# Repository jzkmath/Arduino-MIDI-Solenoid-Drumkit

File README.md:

# Arduino-MIDI-Solenoid-Drumkit
Uses an Arduino Mega and a custom Shield PCB to drive 14 solenoids (RevA) or 32 solenoids (RevB) via MIDI

## Rev A:

## Rev B:

This design is based off the [Adafruit Crikit](https://www.adafruit.com/product/3343) and MIDI Solenoid Drumkit that they did, but instead uses a non-blocking delay and can handle more solenoids. The Solenoids are connected to 5V/12V and a Darlington Array (ULN2003A) connects the negative to ground when turned on. 

Just like in the [Adafuit version](https://learn.adafruit.com/midi-solenoid-drummer/overview), the first solenoid corresponds to a C1 (MIDI Note #24) and the following solenoids correspond to the following notes in chromatic order.

## NOTE:
There is a two pin header (J3) that is the programming jumper. The jumper should be installed here and removed when the Arduino is being programmed. This is because the MIDI Rx line is also use to program the Arduino when its being flashed.

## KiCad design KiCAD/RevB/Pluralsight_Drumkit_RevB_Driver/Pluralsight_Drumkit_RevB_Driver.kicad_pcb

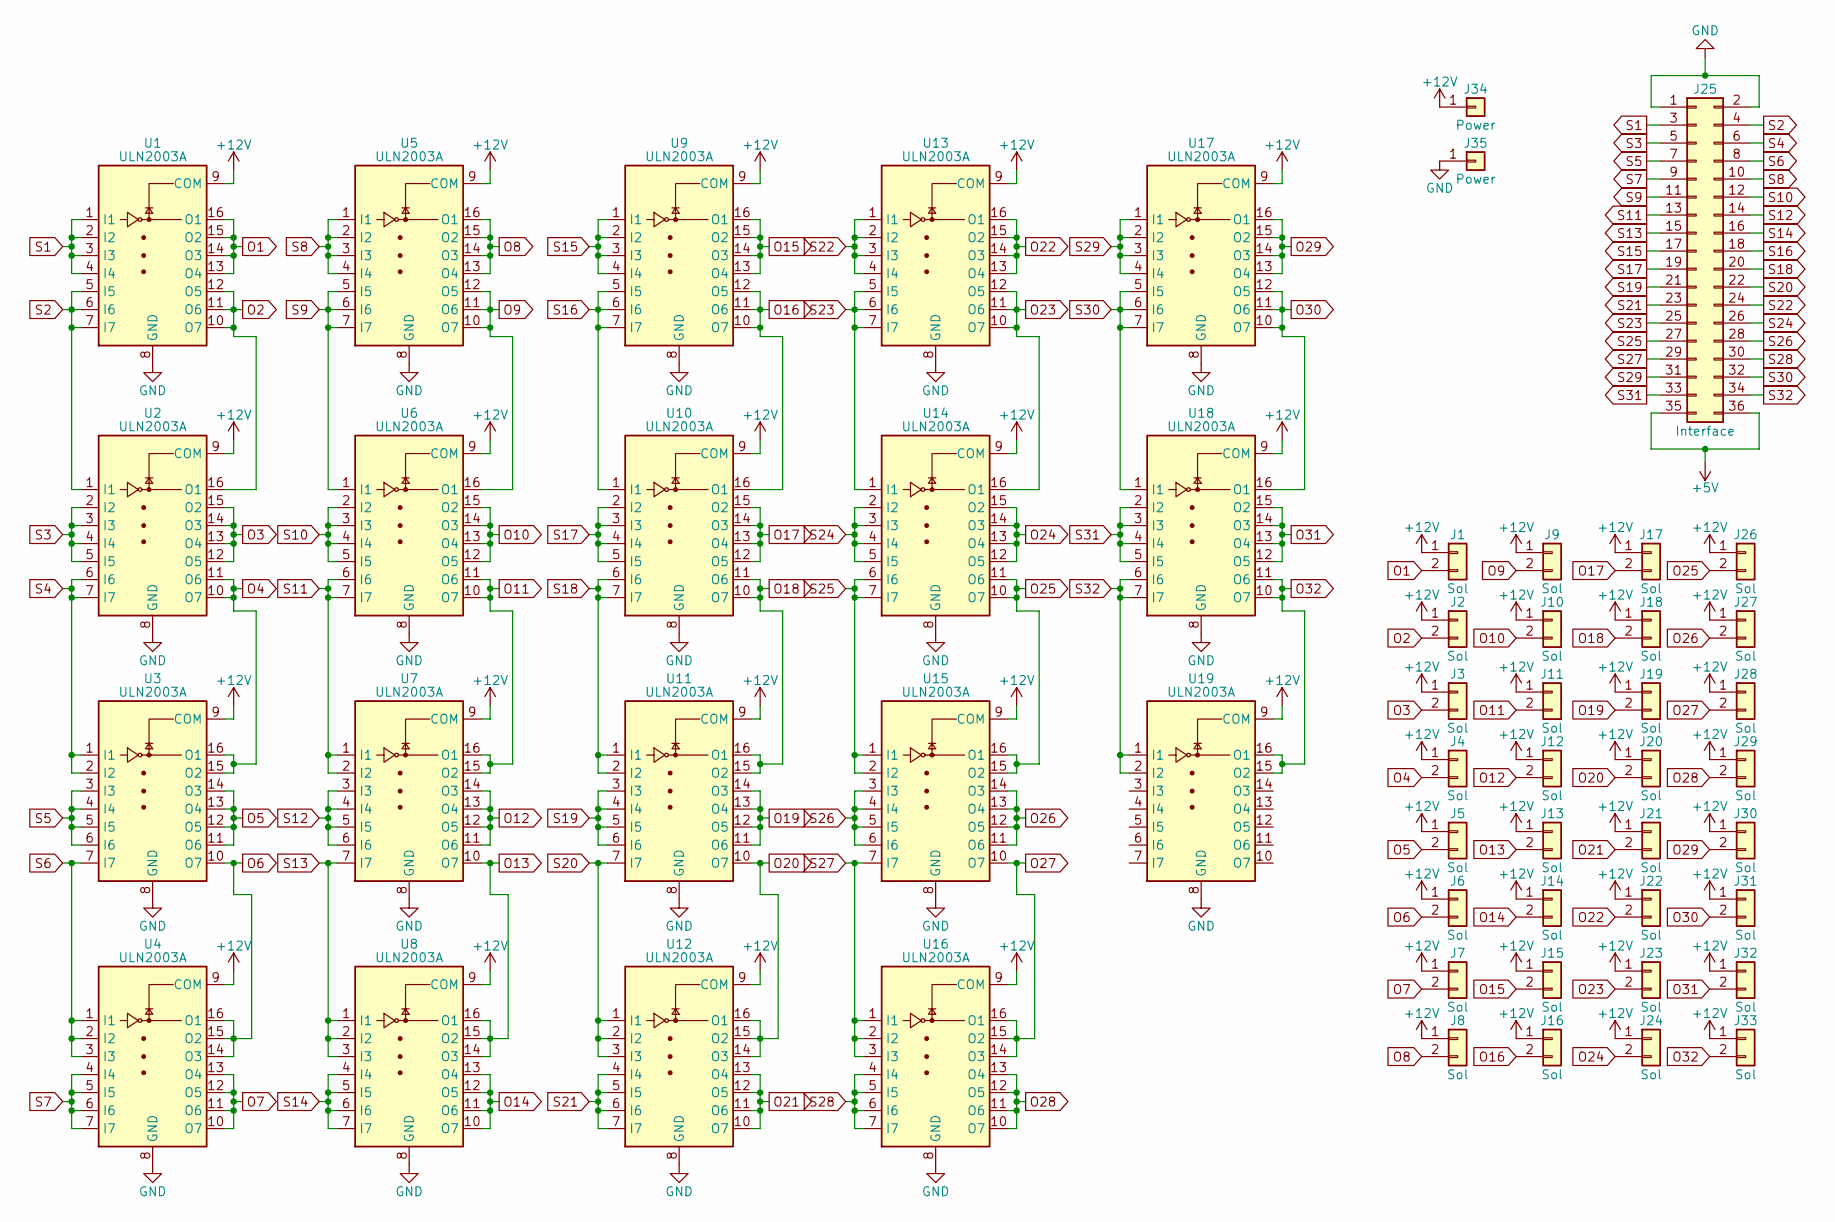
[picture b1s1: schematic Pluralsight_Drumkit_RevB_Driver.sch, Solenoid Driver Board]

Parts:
J1, J2, J3, J4, J5, J6, J7, J8, J9, J10, J11, J12, J13, J14, J15, J16, J17, J18, J19, J20, J21, J22, J23, J24, J26, J27, J28, J29, J30, J31, J32, J33: Sol; ScrewTerm_282834-2
J25: Interface; PinHeader_2x18_P2.54mm_Vertical
J34, J35: Power; SolderPadPower
U1, U2, U3, U4, U5, U6, U7, U8, U9, U10, U11, U12, U13, U14, U15, U16, U17, U18, U19: ULN2003A; DIP-16_W7.62mm_LongPads

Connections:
+12V: J1.1, J2.1, J3.1, J4.1, J5.1, J6.1, J7.1, J8.1, J9.1, J10.1, J11.1, J12.1, J13.1, J14.1, J15.1, J16.1, J17.1, J18.1, J19.1, J20.1, J21.1, J22.1, J23.1, J24.1, J26.1, J27.1, J28.1, J29.1, J30.1, J31.1, J32.1, J33.1, J34.1, U1.9 (COM), U2.9 (COM), U3.9 (COM), U4.9 (COM), U5.9 (COM), U6.9 (COM), U7.9 (COM), U8.9 (COM), U9.9 (COM), U10.9 (COM), U11.9 (COM), U12.9 (COM), U13.9 (COM), U14.9 (COM), U15.9 (COM), U16.9 (COM), U17.9 (COM), U18.9 (COM), U19.9 (COM)
GND: J25.1, J25.2, J35.1, U1.8 (GND), U2.8 (GND), U3.8 (GND), U4.8 (GND), U5.8 (GND), U6.8 (GND), U7.8 (GND), U8.8 (GND), U9.8 (GND), U10.8 (GND), U11.8 (GND), U12.8 (GND), U13.8 (GND), U14.8 (GND), U15.8 (GND), U16.8 (GND), U17.8 (GND), U18.8 (GND), U19.8 (GND)
O1: J1.2, U1.13 (O4), U1.14 (O3), U1.15 (O2), U1.16 (O1)
O2: J2.2, U1.10 (O7), U1.11 (O6), U1.12 (O5), U2.16 (O1)
O3: J3.2, U2.12 (O5), U2.13 (O4), U2.14 (O3), U2.15 (O2)
O4: J4.2, U2.10 (O7), U2.11 (O6), U3.15 (O2), U3.16 (O1)
O5: J5.2, U3.11 (O6), U3.12 (O5), U3.13 (O4), U3.14 (O3)
O6: J6.2, U3.10 (O7), U4.14 (O3), U4.15 (O2), U4.16 (O1)
O7: J7.2, U4.10 (O7), U4.11 (O6), U4.12 (O5), U4.13 (O4)
O8: J8.2, U5.13 (O4), U5.14 (O3), U5.15 (O2), U5.16 (O1)
O9: J9.2, U5.10 (O7), U5.11 (O6), U5.12 (O5), U6.16 (O1)
O10: J10.2, U6.12 (O5), U6.13 (O4), U6.14 (O3), U6.15 (O2)
O11: J11.2, U6.10 (O7), U6.11 (O6), U7.15 (O2), U7.16 (O1)
O12: J12.2, U7.11 (O6), U7.12 (O5), U7.13 (O4), U7.14 (O3)
O13: J13.2, U7.10 (O7), U8.14 (O3), U8.15 (O2), U8.16 (O1)
O14: J14.2, U8.10 (O7), U8.11 (O6), U8.12 (O5), U8.13 (O4)
O15: J15.2, U9.13 (O4), U9.14 (O3), U9.15 (O2), U9.16 (O1)
O16: J16.2, U9.10 (O7), U9.11 (O6), U9.12 (O5), U10.16 (O1)
O17: J17.2, U10.12 (O5), U10.13 (O4), U10.14 (O3), U10.15 (O2)
O18: J18.2, U10.10 (O7), U10.11 (O6), U11.15 (O2), U11.16 (O1)
O19: J19.2, U11.11 (O6), U11.12 (O5), U11.13 (O4), U11.14 (O3)
O20: J20.2, U11.10 (O7), U12.14 (O3), U12.15 (O2), U12.16 (O1)
O21: J21.2, U12.10 (O7), U12.11 (O6), U12.12 (O5), U12.13 (O4)
O22: J22.2, U13.13 (O4), U13.14 (O3), U13.15 (O2), U13.16 (O1)
O23: J23.2, U13.10 (O7), U13.11 (O6), U13.12 (O5), U14.16 (O1)
O24: J24.2, U14.12 (O5), U14.13 (O4), U14.14 (O3), U14.15 (O2)
O25: J26.2, U14.10 (O7), U14.11 (O6), U15.15 (O2), U15.16 (O1)
O26: J27.2, U15.11 (O6), U15.12 (O5), U15.13 (O4), U15.14 (O3)
O27: J28.2, U15.10 (O7), U16.14 (O3), U16.15 (O2), U16.16 (O1)
O28: J29.2, U16.10 (O7), U16.11 (O6), U16.12 (O5), U16.13 (O4)
O29: J30.2, U17.13 (O4), U17.14 (O3), U17.15 (O2), U17.16 (O1)
O30: J31.2, U17.10 (O7), U17.11 (O6), U17.12 (O5), U18.16 (O1)
O31: J32.2, U18.12 (O5), U18.13 (O4), U18.14 (O3), U18.15 (O2)
O32: J33.2, U18.10 (O7), U18.11 (O6), U19.15 (O2), U19.16 (O1)
S1: J25.3, U1.1 (I1), U1.2 (I2), U1.3 (I3), U1.4 (I4)
S2: J25.4, U1.5 (I5), U1.6 (I6), U1.7 (I7), U2.1 (I1)
S3: J25.5, U2.2 (I2), U2.3 (I3), U2.4 (I4), U2.5 (I5)
S4: J25.6, U2.6 (I6), U2.7 (I7), U3.1 (I1), U3.2 (I2)
S5: J25.7, U3.3 (I3), U3.4 (I4), U3.5 (I5), U3.6 (I6)
S6: J25.8, U3.7 (I7), U4.1 (I1), U4.2 (I2), U4.3 (I3)
S7: J25.9, U4.4 (I4), U4.5 (I5), U4.6 (I6), U4.7 (I7)
S8: J25.10, U5.1 (I1), U5.2 (I2), U5.3 (I3), U5.4 (I4)
S9: J25.11, U5.5 (I5), U5.6 (I6), U5.7 (I7), U6.1 (I1)
S10: J25.12, U6.2 (I2), U6.3 (I3), U6.4 (I4), U6.5 (I5)
S11: J25.13, U6.6 (I6), U6.7 (I7), U7.1 (I1), U7.2 (I2)
S12: J25.14, U7.3 (I3), U7.4 (I4), U7.5 (I5), U7.6 (I6)
S13: J25.15, U7.7 (I7), U8.1 (I1), U8.2 (I2), U8.3 (I3)
S14: J25.16, U8.4 (I4), U8.5 (I5), U8.6 (I6), U8.7 (I7)
S15: J25.17, U9.1 (I1), U9.2 (I2), U9.3 (I3), U9.4 (I4)
S16: J25.18, U9.5 (I5), U9.6 (I6), U9.7 (I7), U10.1 (I1)
S17: J25.19, U10.2 (I2), U10.3 (I3), U10.4 (I4), U10.5 (I5)
S18: J25.20, U10.6 (I6), U10.7 (I7), U11.1 (I1), U11.2 (I2)
S19: J25.21, U11.3 (I3), U11.4 (I4), U11.5 (I5), U11.6 (I6)
S20: J25.22, U11.7 (I7), U12.1 (I1), U12.2 (I2), U12.3 (I3)
S21: J25.23, U12.4 (I4), U12.5 (I5), U12.6 (I6), U12.7 (I7)
S22: J25.24, U13.1 (I1), U13.2 (I2), U13.3 (I3), U13.4 (I4)
S23: J25.25, U13.5 (I5), U13.6 (I6), U13.7 (I7), U14.1 (I1)
S24: J25.26, U14.2 (I2), U14.3 (I3), U14.4 (I4), U14.5 (I5)
S25: J25.27, U14.6 (I6), U14.7 (I7), U15.1 (I1), U15.2 (I2)
S26: J25.28, U15.3 (I3), U15.4 (I4), U15.5 (I5), U15.6 (I6)
S27: J25.29, U15.7 (I7), U16.1 (I1), U16.2 (I2), U16.3 (I3)
S28: J25.30, U16.4 (I4), U16.5 (I5), U16.6 (I6), U16.7 (I7)
S29: J25.31, U17.1 (I1), U17.2 (I2), U17.3 (I3), U17.4 (I4)
S30: J25.32, U17.5 (I5), U17.6 (I6), U17.7 (I7), U18.1 (I1)
S31: J25.33, U18.2 (I2), U18.3 (I3), U18.4 (I4), U18.5 (I5)
S32: J25.34, U18.6 (I6), U18.7 (I7), U19.1 (I1), U19.2 (I2)

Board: 2 copper layers, 54 parts (0 on the bottom side), 66 nets, no tracks yet.

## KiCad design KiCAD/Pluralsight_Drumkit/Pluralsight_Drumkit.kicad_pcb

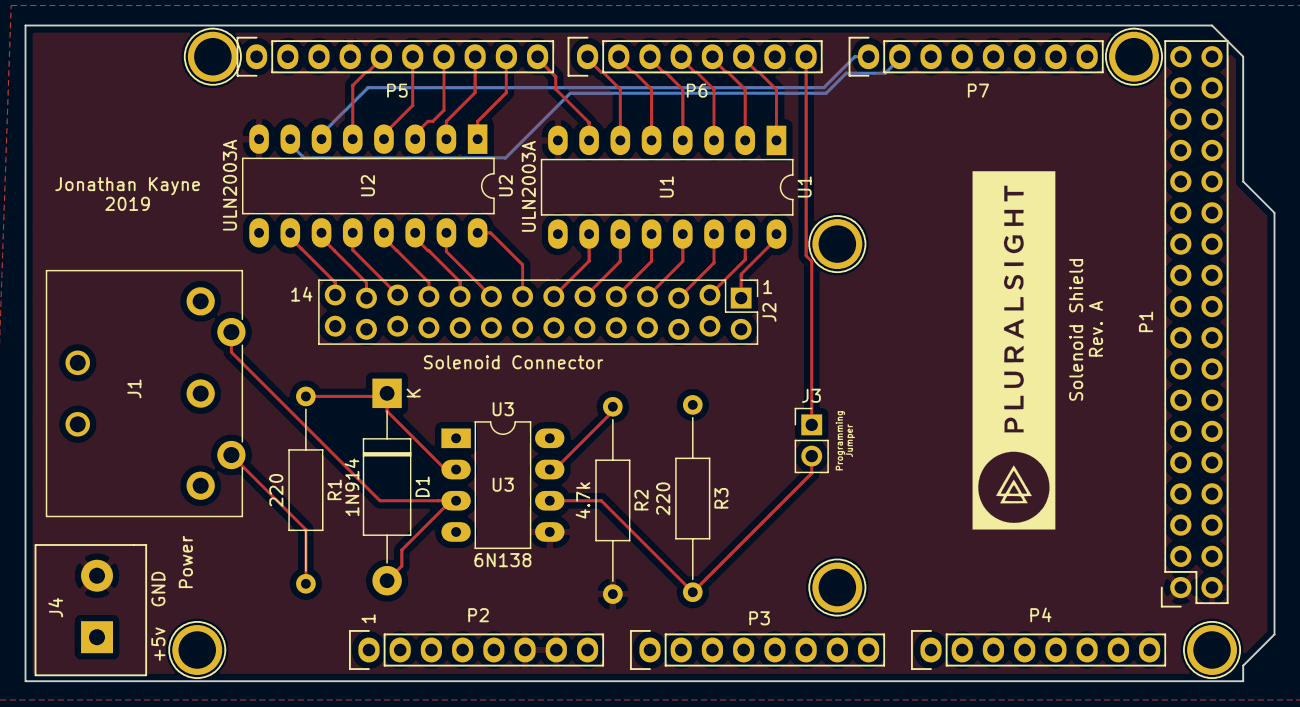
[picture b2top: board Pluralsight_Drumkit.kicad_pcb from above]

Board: 2 copper layers, 101.6 x 53.3 mm, 24 parts (0 on the bottom side), 36 nets.

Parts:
D1: 1N914; D_DO-15_P15.24mm_Horizontal
J1: DIN-5_180degree; SDS-50J
J2: Solenoid Connector; PinHeader_2x14_P2.54mm_Vertical_zigzag
J3: Prog Jumper; PinHeader_1x02_P2.54mm_Vertical
J4: Power; 2_Pos_Screw_Term
P1: Digital; Socket_Strip_Arduino_2x18
P2: Power; Socket_Strip_Arduino_1x08
P3, P4: Analog; Socket_Strip_Arduino_1x08
P5: PWM; Socket_Strip_Arduino_1x10
P6: PWM; Socket_Strip_Arduino_1x08
P7: Communication; Socket_Strip_Arduino_1x08
P8, P9, P10, P11, P12, P13: CONN_01X01; Arduino_1pin
R1, R3: 220; R_Axial_DIN0207_L6.3mm_D2.5mm_P15.24mm_Horizontal
R2: 4.7k; R_Axial_DIN0207_L6.3mm_D2.5mm_P15.24mm_Horizontal
U1, U2: ULN2003A; DIP-16_W7.62mm_LongPads
U3: 6N138; DIP-8_W7.62mm_LongPads

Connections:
+5V: J2.2, J2.4, J2.6, J2.8, J2.10, J2.12, J2.14, J2.16, J2.18, J2.20, J2.22, J2.24, J2.26, J2.28, J4.1, P1.35, P1.36, P2.5, R3.1, U1.9, U2.9, U3.8
/0(Rx0): J3.1, P6.8
/2(**): P6.6, U1.1
/3(**): P6.5, U1.2
/4(**): P6.4, U1.3
/5(**): P6.3, U1.4
/6(**): P6.2, U1.5
/7(**): P6.1, U1.6
/8(**): P5.10, U1.7
/9(**): P5.9, U2.1
/10(**): P5.8, U2.2
/11(**): P5.7, U2.3
/12(**): P5.6, U2.4
/13(**): P5.5, U2.5
/14(Tx3): P7.1, U2.6
/15(Rx3): P7.2, U2.7
GND: J4.2, P1.1, P1.2, P2.6, P2.7, P5.4, R2.2, U1.8, U2.8, U3.5
MIDI_Rx: J3.2, R3.2, U3.6
unnamed: D1.1, R1.1, U3.2
unnamed: D1.2, J1.5, U3.3
unnamed: J1.4, R1.2
unnamed: R2.1, U3.7
S1: J2.1, U1.16
S2: J2.3, U1.15
S3: J2.5, U1.14
S4: J2.7, U1.13
S5: J2.9, U1.12
S6: J2.11, U1.11
S7: J2.13, U1.10
S8: J2.15, U2.16
S9: J2.17, U2.15
S10: J2.19, U2.14
S11: J2.21, U2.13
S12: J2.23, U2.12
S13: J2.25, U2.11
S14: J2.27, U2.10

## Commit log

2019-04-24 Create jkjjk
2019-04-24 Added Arduino Code V1
2019-04-24 Create jjjj
2019-04-24 Added KiCAD files
2019-04-24 Added Gerber and BOM
2019-04-26 Added Digikey BOM
2019-05-06 added RevB
2019-05-24 MocuLUFA hex file
